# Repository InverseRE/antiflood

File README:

Antiflood automation,
Arduino based (inspired by its simplicity).

Please, visit 'doc' directory for details.

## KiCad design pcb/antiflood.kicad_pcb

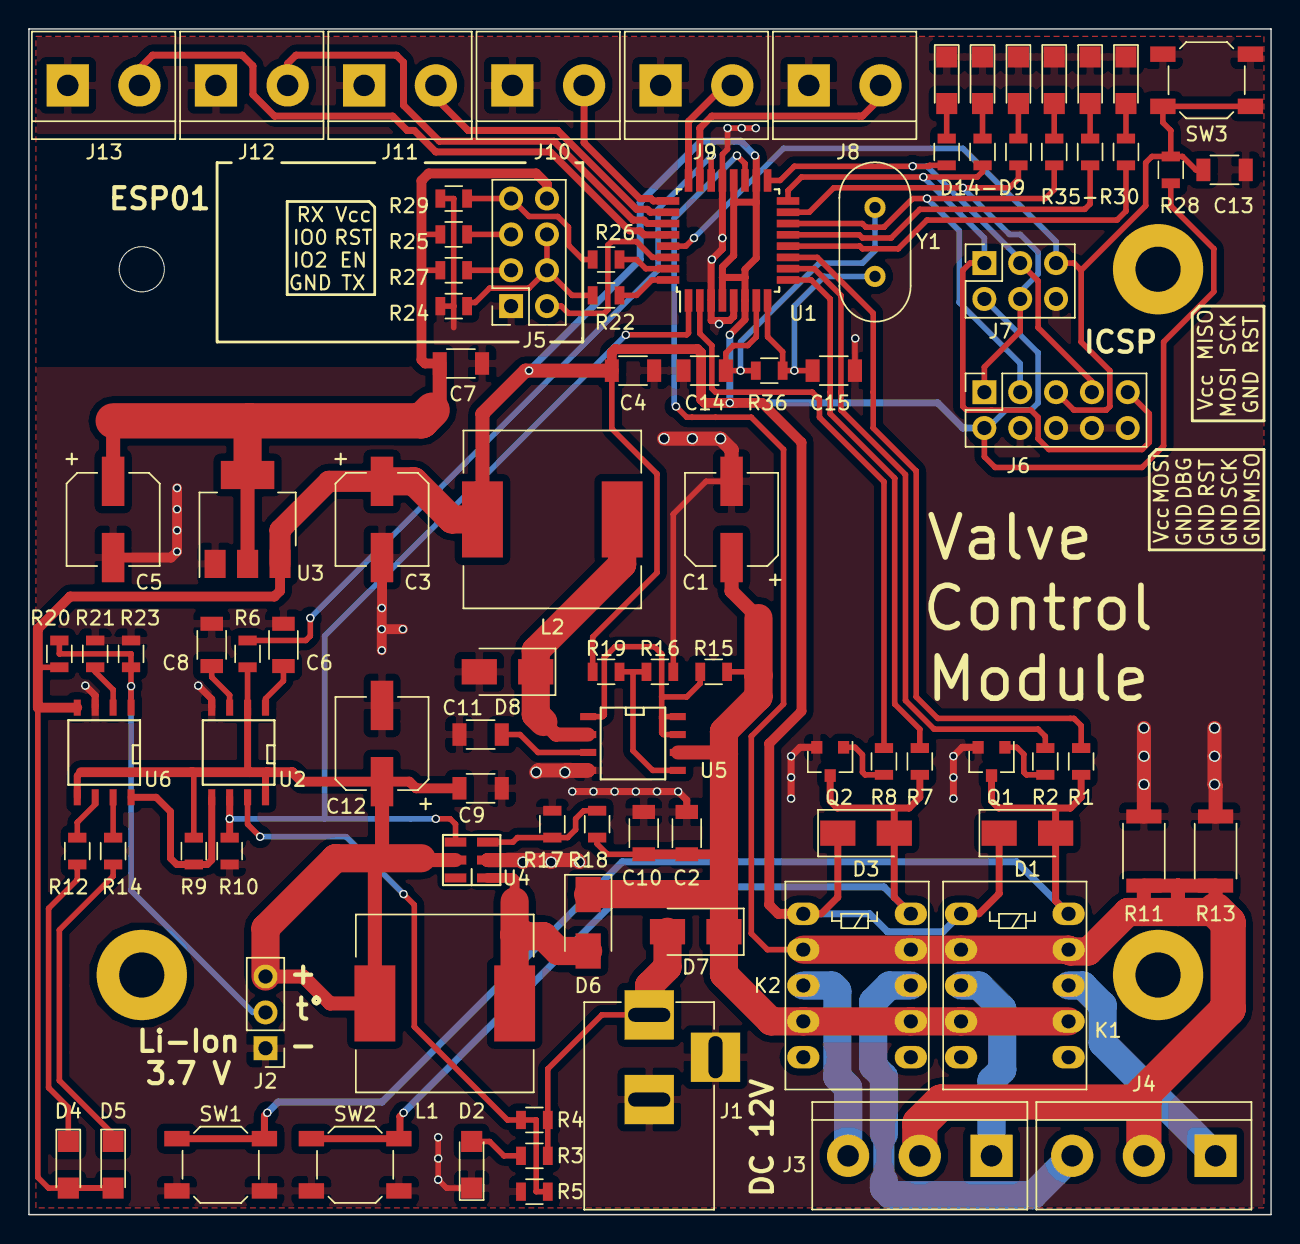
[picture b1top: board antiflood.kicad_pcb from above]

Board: 2 copper layers, 88.0 x 84.0 mm, 82 parts (0 on the bottom side), 58 nets.

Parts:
C1, C5, C12: 100; CP_Elec_6.3x5.7
C2, C4, C6, C7, C8, C13: 0.1; C_1206
C3: 470; CP_Elec_6.3x5.7
C9, C10: 22; C_1206
C11: 470p; C_1206
C14, C15: 22p; C_1206
D1, D3, D8: D; D_SMA
D2, D4, D5: LED; LED_1206
D6, D7: YJ SS14; D_SMA
J1: Barrel_Jack; BARREL_JACK
J2: Conn_01x03_Male; Pin_Header_Straight_1x03_Pitch2.54mm
J3, J4: 01x03; TerminalBlock_bornier-3_P5.08mm
J5: Conn_02x04_Odd_Even; Socket_Strip_Straight_2x04_Pitch2.54mm
J6: Conn_02x05_Odd_Even; Socket_Strip_Straight_2x05_Pitch2.54mm
J7: Conn_02x03_Odd_Even; Socket_Strip_Straight_2x03_Pitch2.54mm
J8, J9, J10, J11, J12, J13: Screw_Terminal_01x02; TerminalBlock_bornier-2_P5.08mm
K1, K2: P-5; Relay_DPDT_FRT5
L1, L2: 220; L_12x12mm_h6mm
Q1, Q2: MMBT3904; SOT-23
R1, R7, R22, R26: 1k5; R_0805
R2, R8: 82; R_0805
R3: 2k; R_0805
R4: 12k; R_0805
R5, R9, R10, R20, R21: 10k; R_0805
R6, R12, R14: 1k; R_0805
R11, R13: 0.5; R_2010
R15: 0.33; R_0805
R16: 1k2; R_0805
R17: 1k05; R_0805
R18: 20k; R_0805
R19: 3k6; R_0805
R23: 19k; R_0805
R24, R25, R27, R28, R29: 3k3; R_0805
R36: 1M; R_0805
SW1, SW2, SW3: SW_Push; SW_SPST_SKQG
U1: ATMEGA328P-AU; TQFP-32_7x7mm_Pitch0.8mm
U2: TL7705; SOIC-8-N
U3: LM1117-3.3; SOT-223-3_TabPin2
U4: MT3608; Ceramic_Filter
U5: MC34063; SOIC-8-N
U6: TP4056; SOIC-8-N
Y1: 16MHz; Crystal_HC49-U_Vertical

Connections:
+3V3: C5.1, C7.1, J5.8, R25.2, R27.2, U3.2
+5V: C3.1, C4.1, D1.1, D3.1, D4.2, D5.2, J6.2, J7.2, K1.1, K2.1, L2.2, R19.1, R20.2, R28.1, U1.4, U1.6, U1.18, U1.20, U3.3, U6.4
+12V: C1.1, C2.1, C10.1, D6.1, D7.1, K1.4, K1.7, K2.4, K2.7, R15.2, R18.1, U5.6
/A0: J8.2, U1.23
/A1: J9.2, U1.24
/A2: J10.2, U1.25
/A3: J11.2, U1.26
/A4: J12.2, U1.27
/A5: J13.2, U1.28
/A6: J3.2, J4.2, K1.2, K1.9, K2.2, K2.9, R11.1, R13.1, U1.19
/A7: R6.2, U1.22
/BAT: C9.1, C12.1, J2.3, L1.1, R6.1, R9.1, U2.2, U2.8, U4.5, U6.5
/BSTE: R10.1, U1.1, U2.6, U4.4
/BTMP: J2.2, R20.1, R23.1, U6.1
/CHGE: R9.2, U2.5, U6.8
/DBG: J6.3, U1.14
/EPWR: R4.2, R5.1, U2.7
/EVSS: D7.2, J1.1, R3.1, R4.1
/FCL: R7.2, U1.9
/FON: R1.2, U1.11
/L3: J6.1, J7.4, U1.15
/L4: J6.9, J7.1, U1.16
/L5: J6.7, J7.3, U1.17
/O1: C14.1, R36.1, U1.7, Y1.1
/O2: C15.1, R36.2, U1.8, Y1.2
/PCL: R8.2, U1.2
/PON: R2.1, U1.10
/RST: C13.1, J6.5, J7.5, R28.2, SW3.1, U1.29
/WCC: R22.2, U1.32
/WRX: J5.2, U1.30
/WTX: R26.2, U1.31
GND: C1.2, C2.2, C3.2, C4.2, C5.2, C6.2, C7.2, C8.2, C9.2, C10.2, C11.2, C12.2, C13.2, C14.2, C15.2, D2.1, D8.2, J1.2, J1.3, J2.1, J5.1, J6.4, J6.6, J6.8, J6.10, J7.6, J8.1, J9.1, J10.1, J11.1, J12.1, J13.1, Q1.2, Q2.2, R5.2, R10.2, R11.2, R13.2, R16.2, R17.2, R21.2, R23.2, R24.2, R29.2, SW1.2, SW2.2, SW3.2, U1.3, U1.5, U1.21, U2.4, U3.1, U4.2, U5.4, U6.3
unnamed: C6.1, U2.1
unnamed: C8.1, U2.3
unnamed: C11.1, U5.3
unnamed: D1.2, K1.10, Q1.3, R1.1, SW1.1
unnamed: D2.2, R3.2
unnamed: D3.2, K2.10, Q2.3, R7.1, SW2.1
unnamed: D4.1, R12.2
unnamed: D5.1, R14.2
unnamed: D6.2, L1.2, U4.1
unnamed: D8.1, L2.1, U5.2
unnamed: J3.1, K1.3
unnamed: J3.3, K2.3
unnamed: J4.1, K1.8
unnamed: J4.3, K2.8
unnamed: J5.3, R27.1
unnamed: J5.4, J5.6, R22.1, R24.1
unnamed: J5.5, R25.1
unnamed: J5.7, R26.1, R29.1
unnamed: Q1.1, R2.2
unnamed: Q2.1, R8.1
unnamed: R12.1, U6.6
unnamed: R14.1, U6.7
unnamed: R15.1, U5.1, U5.7, U5.8
unnamed: R16.1, R19.2, U5.5
unnamed: R17.1, R18.2, U4.3
unnamed: R21.1, U6.2

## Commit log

2002-01-04 Formatting.
2002-01-04 Rename source to firmware.ino.
2018-11-01 Initial commit.
2018-11-01 Place copyright notice and license.
2018-11-05 Update.
2018-11-05 Add label scheme.
2018-11-06 Update readme with states description.
2018-11-07 Update description.
2018-11-07 Fix.
2018-11-07 Add figures.
2018-11-08 Refactor: start.
2018-11-11 Added some manuals and load scripts.
2018-11-11 Improve power save mode. Added button to activate power save from gui.
2018-11-13 Refactor: add a config-variable to hold WiFi mode.
2018-11-16 Trailing spaces.
2018-11-25 Split source code to separate files.
2019-01-18 Add enclosure production requirments.
2019-02-13 Arduino IDE: requires the directory and the main file to be of the same name.
2019-02-13 Refactor: by modules
2019-02-14 Refactor: add module's headers
2019-02-14 Fix: header guards
2019-02-14 Refactor: module naming
    According to Arduino IDE, modules should be named [ino, c, cpp, h]. Behaviour differs.
2019-02-16 WIP: Ticker and Led
2019-02-17 WIP: Probe
2019-02-17 WIP: Valve
2019-02-17 WIP: start WebPage
2019-02-17 Update load scripts.
2019-02-17 Fix app state.
2019-02-17 Fix work in station mode.
2019-02-17 Increased opening/closing time for correct work with low speed valves.
2019-02-17 WIP: App
2019-02-17 WIP: WebPage
2019-02-17 Update debug print. Added raw code for fix time after sleep.
2019-02-18 WIP: NetServer
2019-02-18 WIP: main loop
2019-02-18 WIP: fix build
2019-02-19 Fix. Partially pick 7f27a239121f197854621698293249a8ab5ada23.
2019-02-19 Fix: restore original value.
2019-02-19 WIP: add debug printout.
2019-02-19 Refactor: remove excessive prints.
2019-02-21 Refactor: use separate initializer outside of constructors.
2019-02-23 Bug: override state after run() is constantly IGNORE.
2019-02-23 Bug: undefined behaviour in setting A6/A7 as INPUT
2019-02-23 Fix: valve's op start/stop conditions
2019-02-23 WIP: rework detection
2019-02-24 WIP: reverse direction
2019-02-24 Added raw code for eeprom storage.
2019-02-25 Fix: recharge capacitor from the start
2019-02-25 Improve: better signaling
2019-02-27 Doc: valve's routine description
2019-02-27 Valve: give an extra time for an ongoing action
2019-02-27 WIP: valve manual override
2019-03-02 Fix: pin mapping
2019-03-03 Fix: grant a time for a setup
2019-03-03 Refactor: debug printout / log system
2019-03-03 Refator: stable valve opperations
2019-03-03 Ticker: fixes
2019-03-03 i11: Valve state awarness
    S/W (App, Web) and User are aware of an actual state of valve, as it is
    known to the Valve class.
2019-03-03 update work with eeprom.
2019-03-04 Web: slower redirect
2019-03-04 Debug: use a direct print of any type
2019-03-04 WIP: start Protocol
2019-03-04 Doc: add signal routes
2019-03-04 WIP: define Packet structure
    1) class Packet;
    2) raw data structure;
    3) basic protocol as receive-transmit.
2019-03-05 WIP: add switch by Packet's Class
2019-03-10 Debug: add 0 for one-digit numbers in hex-mode
2019-03-10 Fix: fixes for UDP
    1) add debug printout for net/proto layers
    2) fix WiFiEsp library (https://github.com/bportaluri/WiFiEsp/issues/119)
    3) adjust buffer sizes (do not exceed 255, as byte-type is [0..255])
    4) fix packet validation()
2019-03-10 Doc: debug/network utilities
2019-03-10 Doc: add 'xxd' util usage
2019-03-10 Spelling.
2019-03-18 packet: do not use additional CRC
2019-03-26 scheme: start version 3
2019-03-26 Update scheme.
2019-03-26 scheme: update
2019-03-31 Update work with eeprom. Added unit test.
2019-04-07 Add copyright.
2019-04-08 Ignore all backup files.
2019-04-08 PCB: add borders
2019-04-08 PCB: pre placement of lements
2019-04-11 Schematics: rework power lines
    1. Replace MC34063 with MT3608, which has a plain EN-pin.
    2. Automatic controls on booster and charger.
    3. CPU awarness about external power presence.
    4. CPU awarness of battery voltage.
2019-04-16 Add power supervisor.
2019-04-17 Update: remove linear regul
2019-04-17 Update: pcb-bat connection
2019-04-23 Update: scheme, netlist, pcb
2019-04-30 PCB: power units placement
2019-04-30 PCB: all elements on board
2019-04-30 PCB: alt placement
2019-05-01 PCB: smd transistors, components placement
2019-05-01 PCB: placement before tracks
2019-05-02 PCB: start tracks
2019-05-03 PCB: tracking
2019-05-03 PCB: before filling
2019-05-03 PCB: filled zones
2019-05-03 PCB: references
2019-05-03 PB: text
2019-05-04 PCB: preprint
2019-05-04 PCB: to production
2019-05-08 Update ignore list.
2019-05-08 Probe: add live status
2019-05-22 Probe: auto limiting suspension
    Wait for issue b16 to use this API (enabling/disabling probes).
2019-05-28 Finish proto.
    Add simple commands descriptions.
    Implement iFullState reponse.
2019-05-28 Remarks about (requests) handling module.
2019-05-29 Proto: make response by callback functions.
2019-06-02 WIP: Added setting storage.
2019-06-02 Print graph for all probes.
2019-06-03 IDE: C++ is the major mode.
2019-06-03 Scheduler: add prototype.
2019-06-03 Scheduling: prepare code.
2019-06-03 Scheduler: protocode.
2019-06-03 Scheduler: usage.
2019-06-04 Scheduler: split loops to rerun immediately if forced.
2019-06-04 Debug: less text to consume flash.
2019-06-04 Tasks: times tuning.
2019-06-04 Code style.
2019-06-04 Probes: add software-generated signals.
2019-06-04 Probe: forced signal as an option.
2019-06-04 Doc: add new commands description.
2019-06-05 Predefined server types (for now).
2019-06-07 Scheduler: use local List<T> class.
2019-06-21 Debug: free memory available.
2019-06-21 Notes.
2019-06-23 Fix: rename method to avoid clash of names.
2019-06-25 Fix: in .cpp module initializing with {task, t2g}
2019-06-28 Fixes.
2019-06-28 Fix: warnings.
2019-07-08 Tasks: adjust timings.
2019-07-09 Server task: notes about scheduling.
2019-07-09 Doc: depict events flow.
2019-07-09 Shorten README.
2019-07-09 Copyrights.
2019-07-09 Doc: update.
2019-07-09 App-task forces serv-task.
2019-07-10 Fix work with eeprom settings.
2019-07-16 Power modes: suspend function.
2019-07-17 Idle mode by Timer0 naps.
2019-07-17 Server task forces by events only.
2019-07-25 Sleep: a code acording to description in "avr/sleep.h".
2019-07-25 Refactor.
2019-07-25 Fix: here is no bug.
    Flawless.
    Delay occures if packet arrives at a sleep time.
2019-07-25 Suspend mode: use another timer, resume on UART's rx event.
2019-07-27 Idle power mode: use timer1 instead of timer0; apply a correction.
2019-07-28 Suspend: fixes.
2019-07-30 Power modes: add power down (sleep) mode.
2019-07-31 Fix: probe-signal emulation.
2019-07-31 Refactor: delete an obsolete code.
2019-07-31 Fix: ESP8266 Shield start up with a watchdog.
2019-08-05 Reboot: as a task.
2019-08-05 Fix: buffer for a constant-sized packets.
2019-08-05 Debug: logging levels.
2019-08-05 Debug: messages.
2019-08-06 Raw code to get NTP time.
2019-08-06 User configs: single struct in a memory.
2019-08-07 Doc: reboot task.
2019-08-07 Doc: setting task.
2019-08-07 Doc: network, change user settings.
2019-08-07 Fix: update EEPROM if settings had been changed.
2019-08-08 NTP: skeleton code.
2019-08-08 Net: send to a host (by String name).
2019-08-08 NTP: add setting (pool host).
2019-08-08 NTP: self sustained.
2019-08-09 Fix: sync task restarts others.
2019-08-10 Proto: save/load settings command.
2019-08-11 Doc: sync-task, settings commands.
2019-08-11 Doc: time commands.
2019-08-11 Proto: reboot command.
2019-08-11 S/W reboot: command and the code.
2019-08-11 Proto: power save command.
2019-08-11 Refactor: rename NetServert to a general Net.
2019-08-11 Net: use 'byte' for length and sizes.
2019-08-11 Doc: component sources.
2019-08-13 Add TODO: reboot task tine manage.
2019-08-13 Fix: scheduler do a tick.
2019-08-13 Refactor: reboot task time manage.
2019-08-13 Reboot: H/W signal to a default settings
2019-08-13 Valve: forget an actual state after time passes.
2019-08-29 PCB: components list.
2019-08-29 Tester: initial commit.
2019-08-30 App: procceed.
2019-09-06 License.
2019-10-06 Android mobile app sources.
